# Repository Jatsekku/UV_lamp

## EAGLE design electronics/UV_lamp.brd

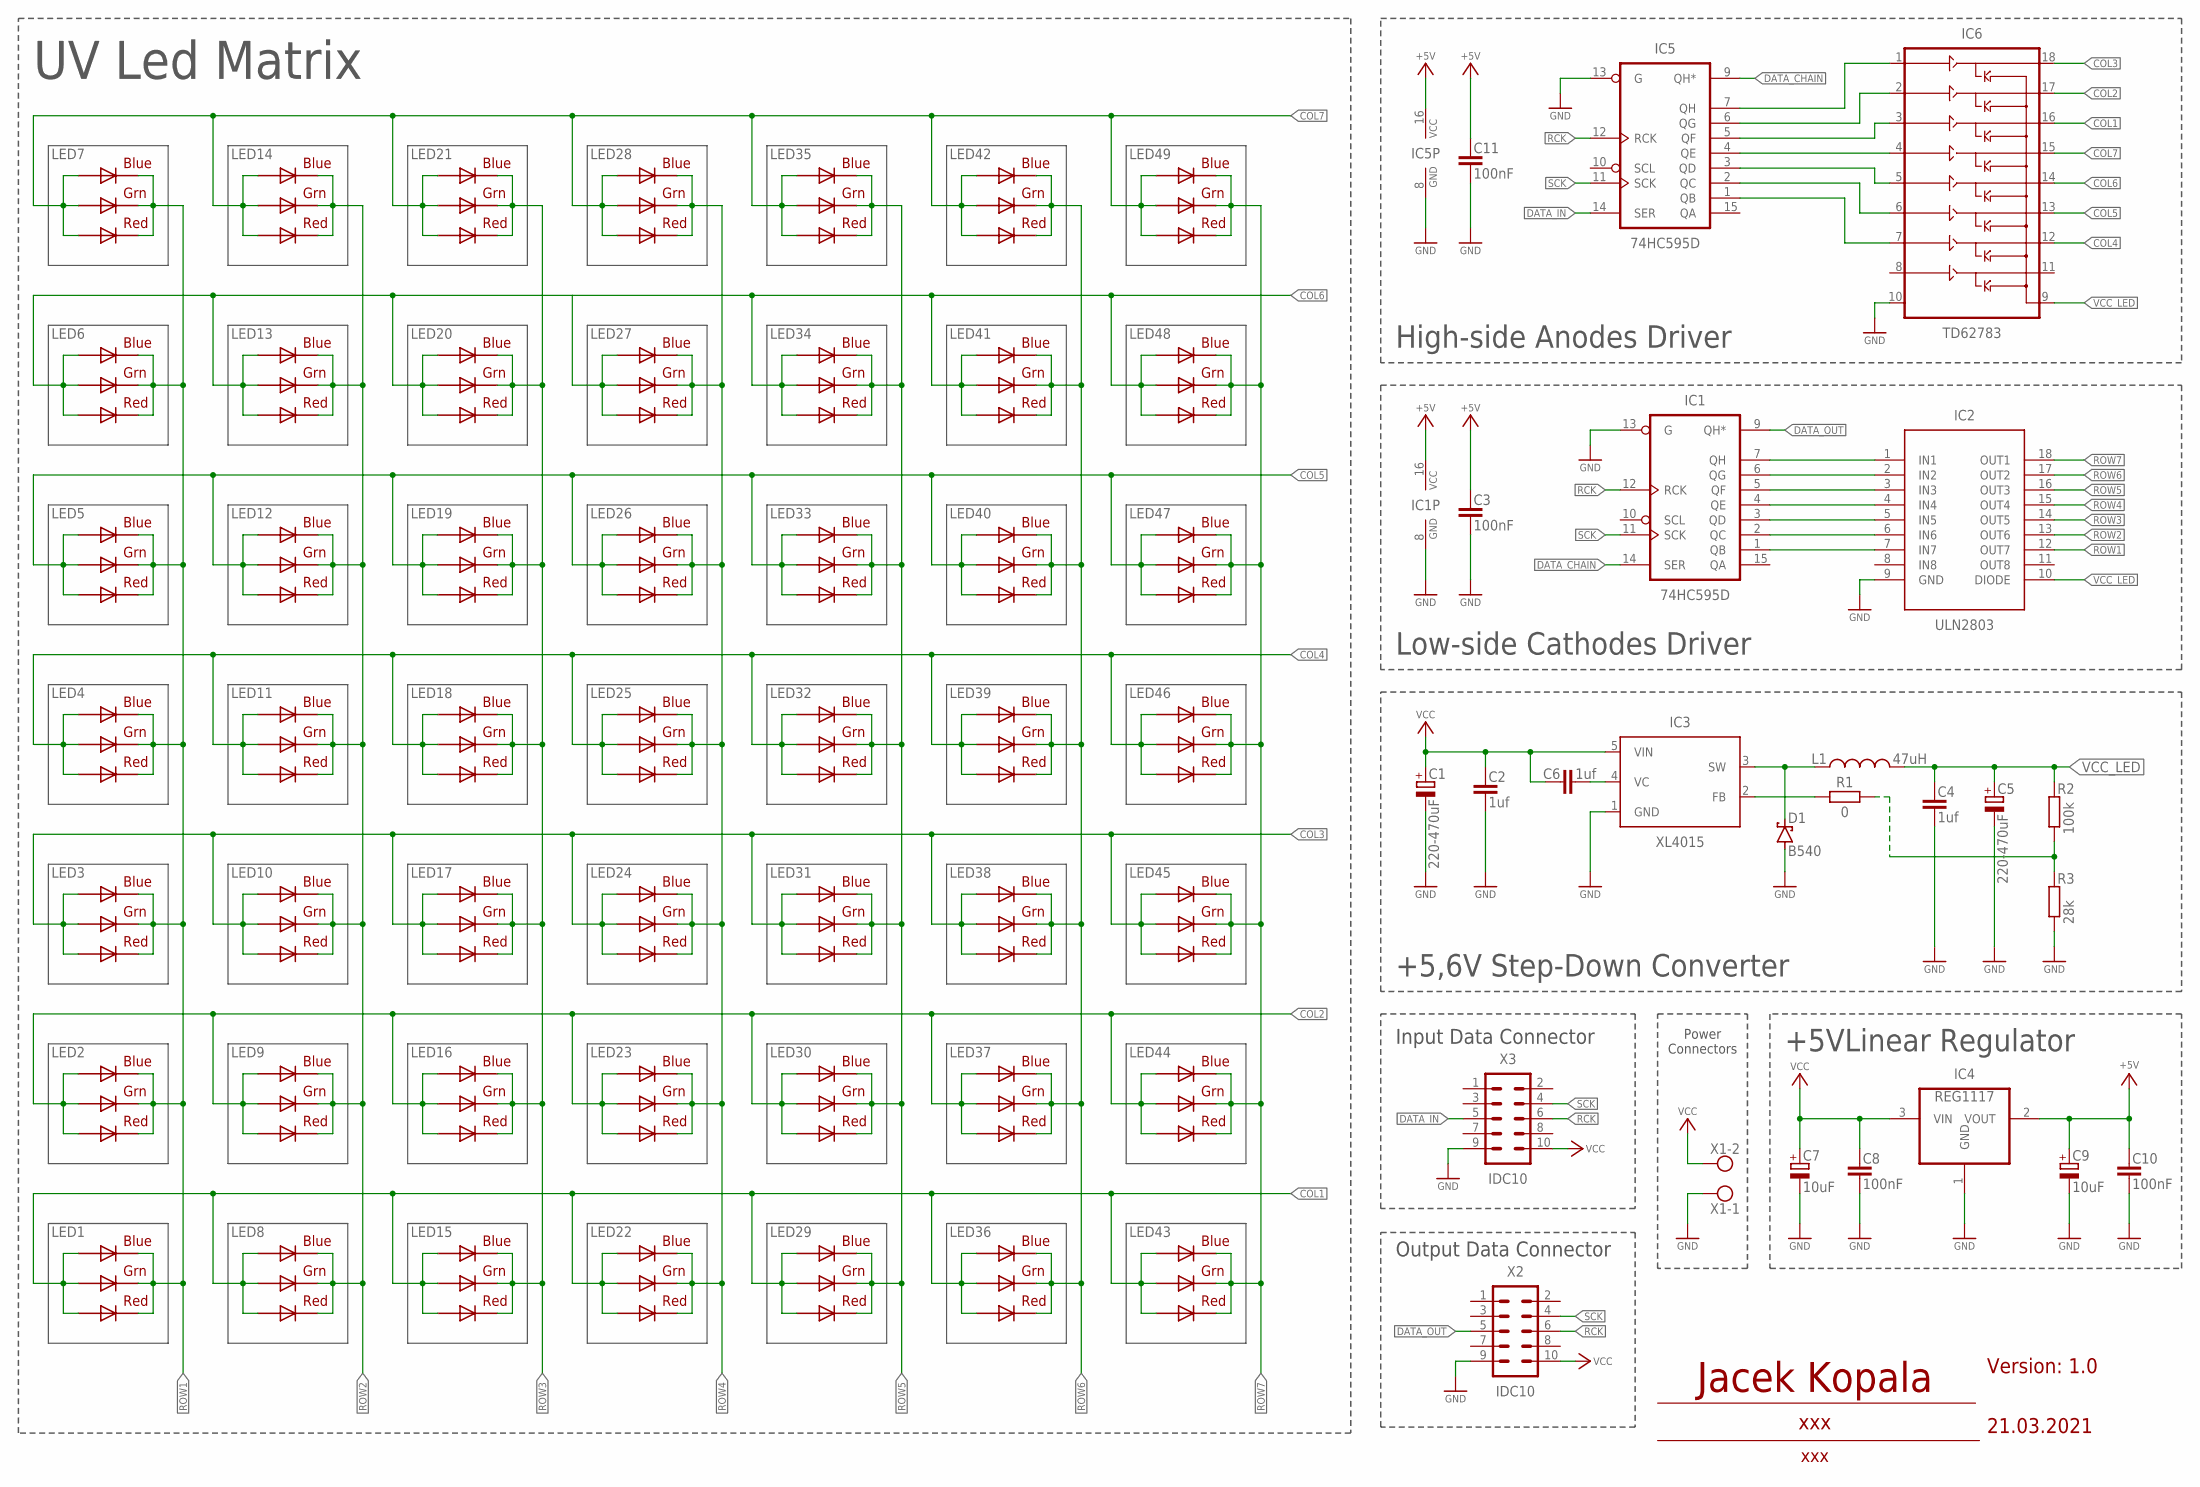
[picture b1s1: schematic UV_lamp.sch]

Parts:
C1, C5: 220-470uF; 140CLH-1010
C2, C4, C6: 1uf; C0805
C3, C8, C10, C11: 100nF; C0805
C7, C9: 10uF; 153CLV-0405
D1: B540; SMC
IC1, IC5: 74HC595D; SO16
IC2: ULN2803; SO18L
IC3: XL4015; TO263-5
IC4: REG1117; SOT223
IC6: TD62783; SO-18L
L1: 47uH; TJ5-U1
LED1, LED2, LED3, LED4, LED5, LED6, LED7, LED8, LED9, LED10, LED11, LED12, LED13, LED14, LED15, LED16, LED17, LED18, LED19, LED20, LED21, LED22, LED23, LED24, LED25, LED26, LED27, LED28, LED29, LED30, LED31, LED32, LED33, LED34, LED35, LED36, LED37, LED38, LED39, LED40, LED41, LED42, LED43, LED44, LED45, LED46, LED47, LED48, LED49: RGBLED5050
R1: 0; R0805
R2: 100k; R0805
R3: 28k; R0805
X1: AK500/2
X2, X3: IDC10; ML10

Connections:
+5V: C3.1, C9.+, C10.1, C11.1, IC1.16 (VCC), IC4.2 (VOUT), IC5.16 (VCC)
COL1: IC6.16 (OUT3), LED1.1 (GREEN_A), LED1.2 (RED_A), LED1.3 (BLUE_A), LED8.1 (GREEN_A), LED8.2 (RED_A), LED8.3 (BLUE_A), LED15.1 (GREEN_A), LED15.2 (RED_A), LED15.3 (BLUE_A), LED22.1 (GREEN_A), LED22.2 (RED_A), LED22.3 (BLUE_A), LED29.1 (GREEN_A), LED29.2 (RED_A), LED29.3 (BLUE_A), LED36.1 (GREEN_A), LED36.2 (RED_A), LED36.3 (BLUE_A), LED43.1 (GREEN_A), LED43.2 (RED_A), LED43.3 (BLUE_A)
COL2: IC6.17 (OUT2), LED2.1 (GREEN_A), LED2.2 (RED_A), LED2.3 (BLUE_A), LED9.1 (GREEN_A), LED9.2 (RED_A), LED9.3 (BLUE_A), LED16.1 (GREEN_A), LED16.2 (RED_A), LED16.3 (BLUE_A), LED23.1 (GREEN_A), LED23.2 (RED_A), LED23.3 (BLUE_A), LED30.1 (GREEN_A), LED30.2 (RED_A), LED30.3 (BLUE_A), LED37.1 (GREEN_A), LED37.2 (RED_A), LED37.3 (BLUE_A), LED44.1 (GREEN_A), LED44.2 (RED_A), LED44.3 (BLUE_A)
COL3: IC6.18 (OUT1), LED3.1 (GREEN_A), LED3.2 (RED_A), LED3.3 (BLUE_A), LED10.1 (GREEN_A), LED10.2 (RED_A), LED10.3 (BLUE_A), LED17.1 (GREEN_A), LED17.2 (RED_A), LED17.3 (BLUE_A), LED24.1 (GREEN_A), LED24.2 (RED_A), LED24.3 (BLUE_A), LED31.1 (GREEN_A), LED31.2 (RED_A), LED31.3 (BLUE_A), LED38.1 (GREEN_A), LED38.2 (RED_A), LED38.3 (BLUE_A), LED45.1 (GREEN_A), LED45.2 (RED_A), LED45.3 (BLUE_A)
COL4: IC6.12 (OUT7), LED4.1 (GREEN_A), LED4.2 (RED_A), LED4.3 (BLUE_A), LED11.1 (GREEN_A), LED11.2 (RED_A), LED11.3 (BLUE_A), LED18.1 (GREEN_A), LED18.2 (RED_A), LED18.3 (BLUE_A), LED25.1 (GREEN_A), LED25.2 (RED_A), LED25.3 (BLUE_A), LED32.1 (GREEN_A), LED32.2 (RED_A), LED32.3 (BLUE_A), LED39.1 (GREEN_A), LED39.2 (RED_A), LED39.3 (BLUE_A), LED46.1 (GREEN_A), LED46.2 (RED_A), LED46.3 (BLUE_A)
COL5: IC6.13 (OUT6), LED5.1 (GREEN_A), LED5.2 (RED_A), LED5.3 (BLUE_A), LED12.1 (GREEN_A), LED12.2 (RED_A), LED12.3 (BLUE_A), LED19.1 (GREEN_A), LED19.2 (RED_A), LED19.3 (BLUE_A), LED26.1 (GREEN_A), LED26.2 (RED_A), LED26.3 (BLUE_A), LED33.1 (GREEN_A), LED33.2 (RED_A), LED33.3 (BLUE_A), LED40.1 (GREEN_A), LED40.2 (RED_A), LED40.3 (BLUE_A), LED47.1 (GREEN_A), LED47.2 (RED_A), LED47.3 (BLUE_A)
COL6: IC6.14 (OUT5), LED6.1 (GREEN_A), LED6.2 (RED_A), LED6.3 (BLUE_A), LED13.1 (GREEN_A), LED13.2 (RED_A), LED13.3 (BLUE_A), LED20.1 (GREEN_A), LED20.2 (RED_A), LED20.3 (BLUE_A), LED27.1 (GREEN_A), LED27.2 (RED_A), LED27.3 (BLUE_A), LED34.1 (GREEN_A), LED34.2 (RED_A), LED34.3 (BLUE_A), LED41.1 (GREEN_A), LED41.2 (RED_A), LED41.3 (BLUE_A), LED48.1 (GREEN_A), LED48.2 (RED_A), LED48.3 (BLUE_A)
COL7: IC6.15 (OUT4), LED7.1 (GREEN_A), LED7.2 (RED_A), LED7.3 (BLUE_A), LED14.1 (GREEN_A), LED14.2 (RED_A), LED14.3 (BLUE_A), LED21.1 (GREEN_A), LED21.2 (RED_A), LED21.3 (BLUE_A), LED28.1 (GREEN_A), LED28.2 (RED_A), LED28.3 (BLUE_A), LED35.1 (GREEN_A), LED35.2 (RED_A), LED35.3 (BLUE_A), LED42.1 (GREEN_A), LED42.2 (RED_A), LED42.3 (BLUE_A), LED49.1 (GREEN_A), LED49.2 (RED_A), LED49.3 (BLUE_A)
DATA_CHAIN: IC1.14 (SER), IC5.9 (QH*)
DATA_IN: IC5.14 (SER), X3.5
DATA_OUT: IC1.9 (QH*), X2.5
GND: C1.-, C2.2, C3.2, C4.2, C5.-, C7.-, C8.2, C9.-, C10.2, C11.2, D1.A, IC1.8 (GND), IC1.13 (G), IC2.9 (GND), IC3.1 (GND), IC4.1 (GND), IC5.8 (GND), IC5.13 (G), IC6.10 (VS), R3.1, X1.1, X2.9, X3.9
unnamed: IC1.7 (QH), IC2.1 (IN1)
unnamed: IC1.6 (QG), IC2.2 (IN2)
unnamed: IC1.5 (QF), IC2.3 (IN3)
unnamed: IC5.4 (QE), IC6.4 (IN4)
unnamed: IC1.4 (QE), IC2.4 (IN4)
unnamed: IC1.3 (QD), IC2.5 (IN5)
unnamed: IC1.2 (QC), IC2.6 (IN6)
unnamed: IC1.1 (QB), IC2.7 (IN7)
unnamed: IC5.3 (QD), IC6.5 (IN5)
unnamed: IC5.2 (QC), IC6.6 (IN6)
unnamed: IC5.1 (QB), IC6.7 (IN7)
unnamed: IC5.5 (QF), IC6.3 (IN3)
unnamed: IC5.6 (QG), IC6.2 (IN2)
unnamed: IC5.7 (QH), IC6.1 (IN1)
unnamed: C6.1, IC3.4 (VC)
unnamed: D1.C, IC3.3 (SW), L1.1
unnamed: IC3.2 (FB), R1.2
unnamed: R1.1, R2.1, R3.2
RCK: IC1.12 (RCK), IC5.12 (RCK), X2.6, X3.6
ROW1: IC2.12 (OUT7), LED1.4 (BLUE_C), LED1.5 (RED_C), LED1.6 (GREEN_C), LED2.4 (BLUE_C), LED2.5 (RED_C), LED2.6 (GREEN_C), LED3.4 (BLUE_C), LED3.5 (RED_C), LED3.6 (GREEN_C), LED4.4 (BLUE_C), LED4.5 (RED_C), LED4.6 (GREEN_C), LED5.4 (BLUE_C), LED5.5 (RED_C), LED5.6 (GREEN_C), LED6.4 (BLUE_C), LED6.5 (RED_C), LED6.6 (GREEN_C), LED7.4 (BLUE_C), LED7.5 (RED_C), LED7.6 (GREEN_C)
ROW2: IC2.13 (OUT6), LED8.4 (BLUE_C), LED8.5 (RED_C), LED8.6 (GREEN_C), LED9.4 (BLUE_C), LED9.5 (RED_C), LED9.6 (GREEN_C), LED10.4 (BLUE_C), LED10.5 (RED_C), LED10.6 (GREEN_C), LED11.4 (BLUE_C), LED11.5 (RED_C), LED11.6 (GREEN_C), LED12.4 (BLUE_C), LED12.5 (RED_C), LED12.6 (GREEN_C), LED13.4 (BLUE_C), LED13.5 (RED_C), LED13.6 (GREEN_C), LED14.4 (BLUE_C), LED14.5 (RED_C), LED14.6 (GREEN_C)
ROW3: IC2.14 (OUT5), LED15.4 (BLUE_C), LED15.5 (RED_C), LED15.6 (GREEN_C), LED16.4 (BLUE_C), LED16.5 (RED_C), LED16.6 (GREEN_C), LED17.4 (BLUE_C), LED17.5 (RED_C), LED17.6 (GREEN_C), LED18.4 (BLUE_C), LED18.5 (RED_C), LED18.6 (GREEN_C), LED19.4 (BLUE_C), LED19.5 (RED_C), LED19.6 (GREEN_C), LED20.4 (BLUE_C), LED20.5 (RED_C), LED20.6 (GREEN_C), LED21.4 (BLUE_C), LED21.5 (RED_C), LED21.6 (GREEN_C)
ROW4: IC2.15 (OUT4), LED22.4 (BLUE_C), LED22.5 (RED_C), LED22.6 (GREEN_C), LED23.4 (BLUE_C), LED23.5 (RED_C), LED23.6 (GREEN_C), LED24.4 (BLUE_C), LED24.5 (RED_C), LED24.6 (GREEN_C), LED25.4 (BLUE_C), LED25.5 (RED_C), LED25.6 (GREEN_C), LED26.4 (BLUE_C), LED26.5 (RED_C), LED26.6 (GREEN_C), LED27.4 (BLUE_C), LED27.5 (RED_C), LED27.6 (GREEN_C), LED28.4 (BLUE_C), LED28.5 (RED_C), LED28.6 (GREEN_C)
ROW5: IC2.16 (OUT3), LED29.4 (BLUE_C), LED29.5 (RED_C), LED29.6 (GREEN_C), LED30.4 (BLUE_C), LED30.5 (RED_C), LED30.6 (GREEN_C), LED31.4 (BLUE_C), LED31.5 (RED_C), LED31.6 (GREEN_C), LED32.4 (BLUE_C), LED32.5 (RED_C), LED32.6 (GREEN_C), LED33.4 (BLUE_C), LED33.5 (RED_C), LED33.6 (GREEN_C), LED34.4 (BLUE_C), LED34.5 (RED_C), LED34.6 (GREEN_C), LED35.4 (BLUE_C), LED35.5 (RED_C), LED35.6 (GREEN_C)
ROW6: IC2.17 (OUT2), LED36.4 (BLUE_C), LED36.5 (RED_C), LED36.6 (GREEN_C), LED37.4 (BLUE_C), LED37.5 (RED_C), LED37.6 (GREEN_C), LED38.4 (BLUE_C), LED38.5 (RED_C), LED38.6 (GREEN_C), LED39.4 (BLUE_C), LED39.5 (RED_C), LED39.6 (GREEN_C), LED40.4 (BLUE_C), LED40.5 (RED_C), LED40.6 (GREEN_C), LED41.4 (BLUE_C), LED41.5 (RED_C), LED41.6 (GREEN_C), LED42.4 (BLUE_C), LED42.5 (RED_C), LED42.6 (GREEN_C)
ROW7: IC2.18 (OUT1), LED43.4 (BLUE_C), LED43.5 (RED_C), LED43.6 (GREEN_C), LED44.4 (BLUE_C), LED44.5 (RED_C), LED44.6 (GREEN_C), LED45.4 (BLUE_C), LED45.5 (RED_C), LED45.6 (GREEN_C), LED46.4 (BLUE_C), LED46.5 (RED_C), LED46.6 (GREEN_C), LED47.4 (BLUE_C), LED47.5 (RED_C), LED47.6 (GREEN_C), LED48.4 (BLUE_C), LED48.5 (RED_C), LED48.6 (GREEN_C), LED49.4 (BLUE_C), LED49.5 (RED_C), LED49.6 (GREEN_C)
SCK: IC1.11 (SCK), IC5.11 (SCK), X2.4, X3.4
VCC: C1.+, C2.1, C6.2, C7.+, C8.1, IC3.5 (VIN), IC4.3 (VIN), X1.2, X2.10, X3.10
VCC_LED: C4.1, C5.+, IC2.10 (DIODE), IC6.9 (GND), L1.2, R2.2

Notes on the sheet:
+5VLinear Regulator
Power Connectors
UV Led Matrix
High-side Anodes Driver
Low-side Cathodes Driver
Input Data Connector
Output Data Connector
+5,6V Step-Down Converter
21.03.2021
Version: 1.0
Jacek Kopala
xxx

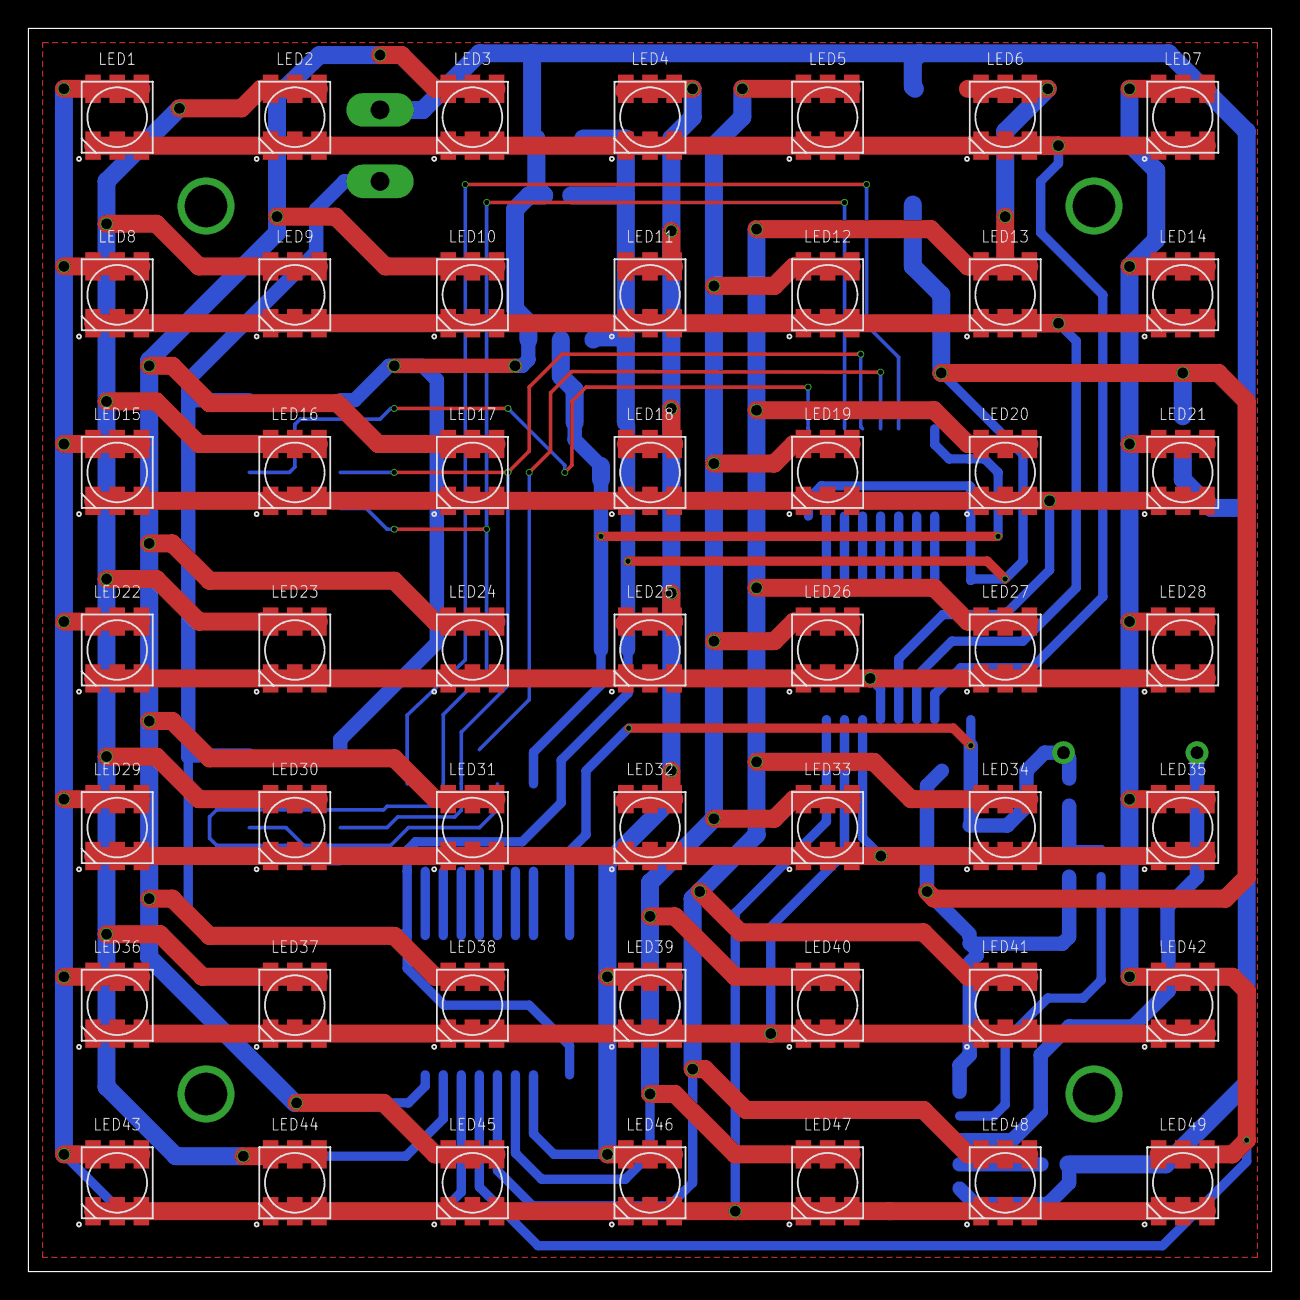
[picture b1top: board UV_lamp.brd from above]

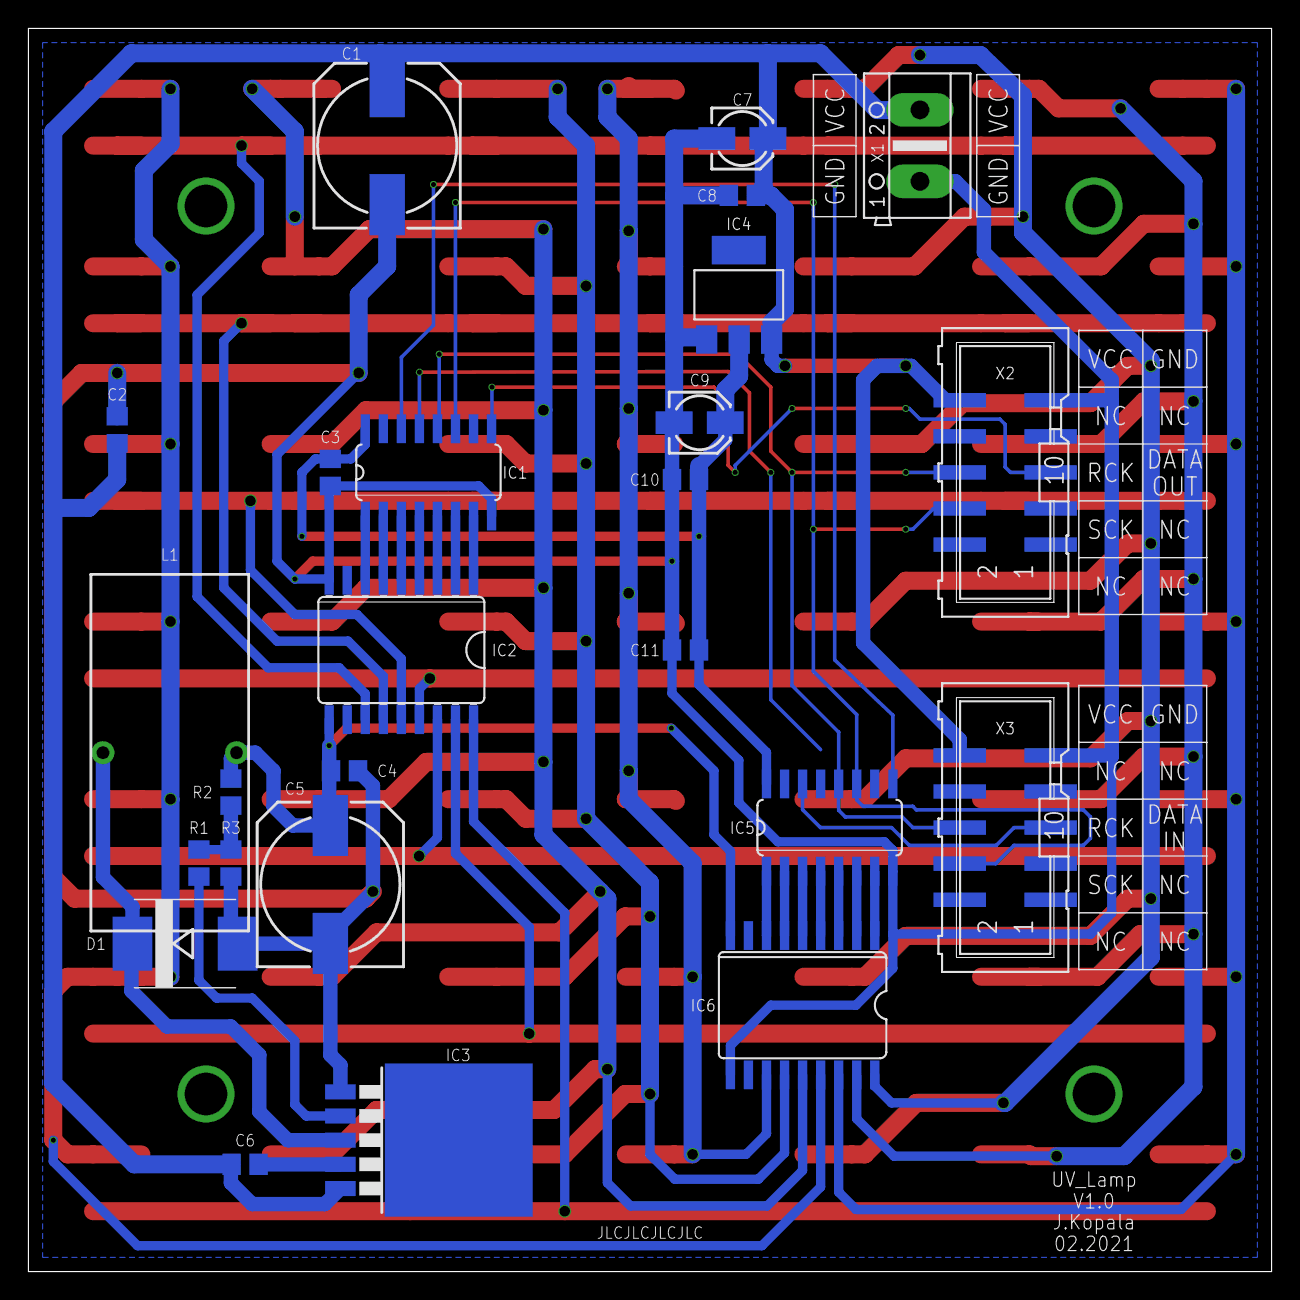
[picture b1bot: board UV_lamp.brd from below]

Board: 2 copper layers, 87.5 x 87.5 mm, 74 parts (25 on the bottom side), 41 nets.
